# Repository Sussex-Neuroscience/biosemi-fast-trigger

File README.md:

# biosemi-fast-trigger
System for fast triggering in Biosemi EEG systems

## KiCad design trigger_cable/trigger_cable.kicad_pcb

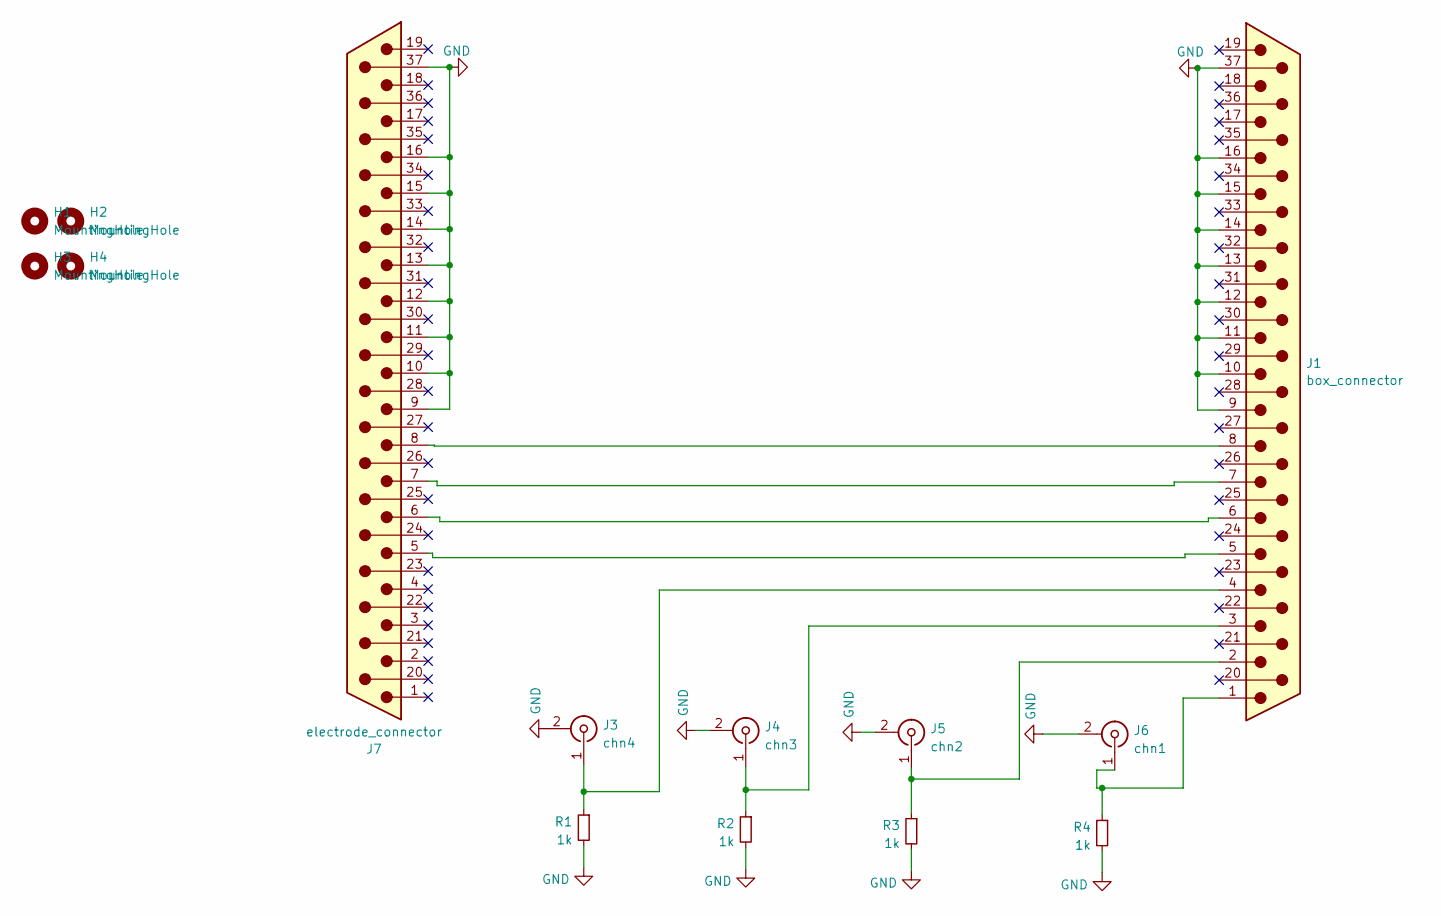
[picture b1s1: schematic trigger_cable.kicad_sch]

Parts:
H1, H2, H3, H4: MountingHole; MountingHole_3.2mm_M3
J1: box_connector; DSUB-37_Male_Horizontal_P2.77x2.54mm_EdgePinOffset9.40mm
J3: chn4; BNC_Amphenol_B6252HB-NPP3G-50_Horizontal
J4: chn3; BNC_Amphenol_B6252HB-NPP3G-50_Horizontal
J5: chn2; BNC_Amphenol_B6252HB-NPP3G-50_Horizontal
J6: chn1; BNC_Amphenol_B6252HB-NPP3G-50_Horizontal
J7: electrode_connector; DSUB-37_Female_Horizontal_P2.77x2.54mm_EdgePinOffset9.40mm
R1, R2, R3, R4: 1k; R_Axial_DIN0309_L9.0mm_D3.2mm_P12.70mm_Horizontal

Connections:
GND: J1.9, J1.10, J1.11, J1.12, J1.13, J1.14, J1.15, J1.16, J1.37, J3.2 (Ext), J4.2 (Ext), J5.2 (Ext), J6.2 (Ext), J7.9, J7.10, J7.11, J7.12, J7.13, J7.14, J7.15, J7.16, J7.37, R1.2, R2.2, R3.2, R4.2
unnamed: J1.5, J7.5
unnamed: J1.6, J7.6
unnamed: J1.7, J7.7
unnamed: J1.8, J7.8
unnamed: J1.4, J3.1 (In), R1.1
unnamed: J1.3, J4.1 (In), R2.1
unnamed: J1.2, J5.1 (In), R3.1
unnamed: J1.1, J6.1 (In), R4.1

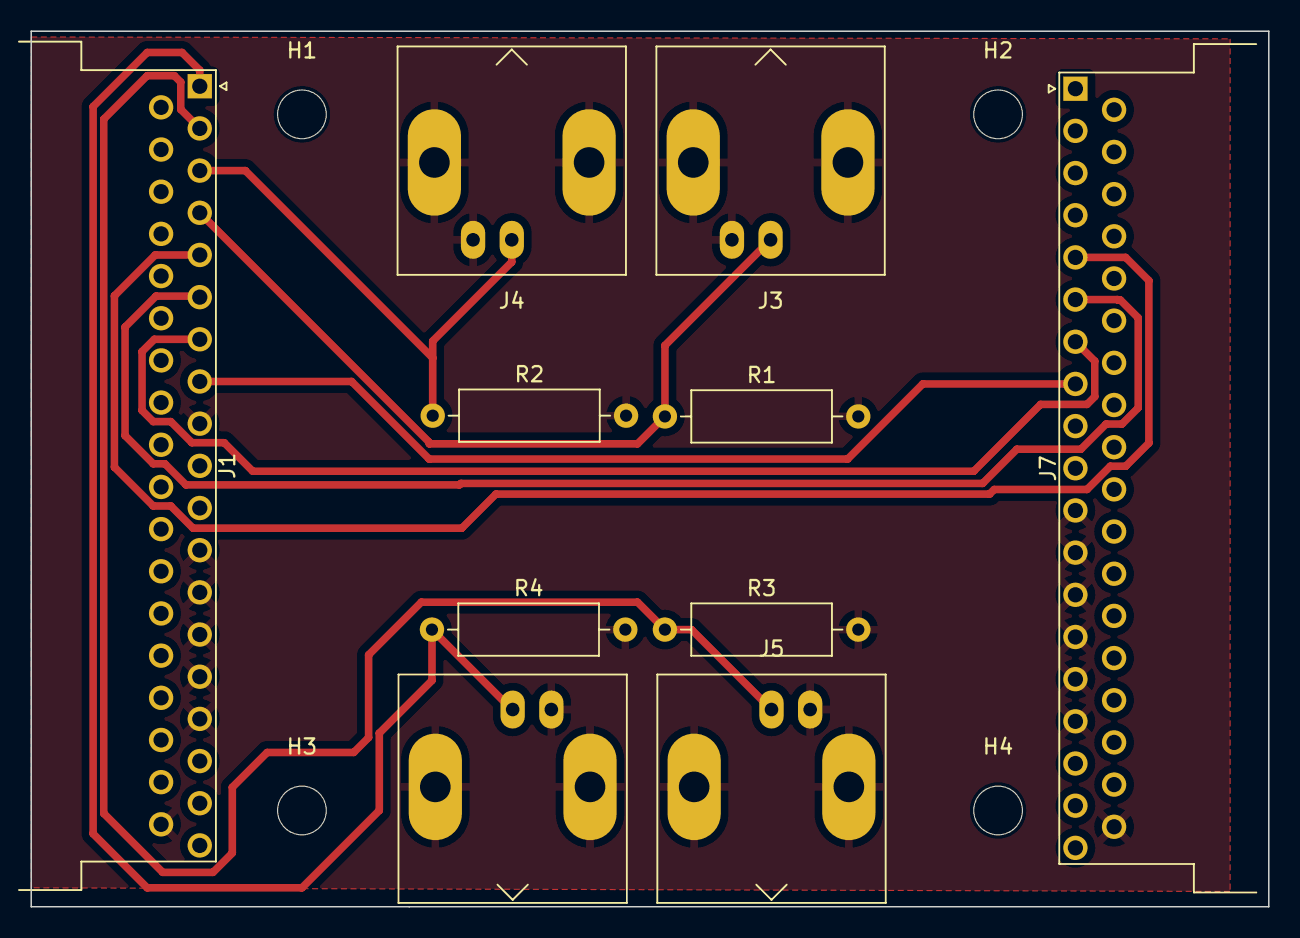
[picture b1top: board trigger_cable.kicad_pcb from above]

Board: 2 copper layers, 81.3 x 57.5 mm, 14 parts (0 on the bottom side), 9 nets.

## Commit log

2023-01-26 start adding documentation and designs
2023-01-26 initial documentation and bom
2023-01-26 update bom
2023-08-04 first pcb version
2023-08-22 update board for production
2023-08-22 update for production
2023-09-29 update system
2024-08-21 revamp project, so that detection and triggering is done via Arduino
2024-09-23 work on the enclosure
